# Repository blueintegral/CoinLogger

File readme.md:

CoinLogger
==========

CoinLogger is a US Quarter sized data logging platform. The current incantation has an accelerometer on it and 8 MB of Flash storage. It is based on the ATTiny85 microcontroller and also includes a USB port for retrieving the captured data. It was designed with a small size and extremely low power consumption in mind.

NanoLogger is a smaller version of CoinLogger, coming in at about the size of a dime, just over 15mm across. It doesn't have a USB port because there's no room. Instead, you need something like this: https://www.sparkfun.com/products/9235. The battery is smaller, so the battery life is substantially less, and programming and reading data off the device is done via small pads below the battery. This is best done with pogo pins, or you can solder to them. NanoLogger was designed to sacrifice some usability in exchange for an extremely small size.

Uses:
-----
* Amateur rocketry
* Tracking and alerting upon concussions in impact sports
* Characterizing your favorite rollercoaster
* Whatever else you can think of

Future Plans:
-------------
* Add versions with more/different sensors
* Make it even smaller
* Make a version that uses energy harvesting and remove the need for a battery
* Add a low power transciever?
* Move to FRAM instead of Flash, since FRAM can be lower power

Current State:
--------------
Version 1.1 of the boards has been fabbed and is being tested. Firmware is still being written. A program to pull data off the device over USB is also under development. 

Fabbed v1.1 CoinLogger:

Fabbed v1 NanoLogger:

Old v1:

Breadboarded circuit:

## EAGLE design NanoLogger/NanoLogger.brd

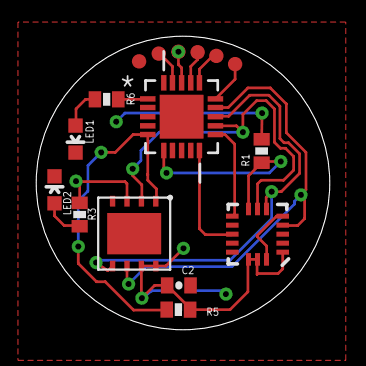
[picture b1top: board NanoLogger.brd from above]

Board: 4 copper layers, 16.3 x 16.3 mm, 17 parts (1 on the bottom side), 16 nets.

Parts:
/RESET: TPTP08R; TP08R
C2: 0.1uF; 0402-CAP
GND: TPTP08R; TP08R
LED1, LED2: LED-0603
MISO: TPTP08R; TP08R
MOSI: TPTP08R; TP08R
R1, R5: 10k; 0402-RES
R3, R6: 470; 0402-RES
SCK: TPTP08R; TP08R
U1: ATTINY2313-20MU; QFN50P400X400X80-21N
U4: LIS331; LGA16-3MM
U$1: ML621-TZ1
U$2: MX25U8035EZUI-10G
VCC: TPTP08R; TP08R

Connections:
ADI: U1.13, U4.6, U$2.5
ADO: U1.12, U4.7, U$2.2
ASCK: U1.14, U4.4, U$2.6
GND: C2.2, GND.TP, LED1.C, LED2.C, R1.2, U1.8, U1.21, U4.5, U4.10, U4.12, U4.13, U4.16, U$1.P$2, U$2.4, U$2.9
IMUCS: R1.1, U1.6, U4.8
INT1: U1.10, U4.11
INT2: U1.11, U4.9
MEMCS: R5.1, U1.5, U$2.1
unnamed: R6.2, U1.1
unnamed: /RESET.TP, U1.19
unnamed: LED2.A, R3.1
unnamed: SCK.TP, U1.17
unnamed: LED1.A, R6.1
unnamed: MISO.TP, U1.16
unnamed: MOSI.TP, U1.15
VCC: C2.1, R3.2, R5.2, U1.18, U4.1, U4.14, U4.15, U$1.P$1, U$2.3, U$2.7, U$2.8, VCC.TP

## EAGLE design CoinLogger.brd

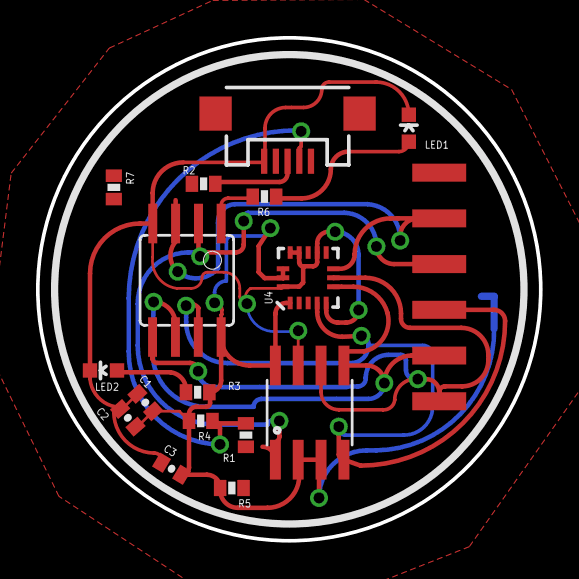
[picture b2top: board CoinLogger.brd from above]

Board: 2 copper layers, 27.9 x 27.9 mm, 18 parts (1 on the bottom side), 12 nets.

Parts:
BAT1: BATTCON_20MM
C1, C3: 10uF; 0402-CAP
C2: 0.1uF; 0402-CAP
IC1: TINY11S; SOIC8
JP2: 1X06-SMD_EDGE
LED1, LED2: LED-0603
R1, R2: 68; 0402-RES
R3, R6: 470; 0402-RES
R4: 1.5k; 0402-RES
R5: 10k; 0402-RES
R7: 4.7k; 0402-RES
U4: LIS331; LGA16-3MM
U$1: W25Q80BV; SOIC8
X1: USB-MICROB

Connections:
GND: BAT1.2, C1.2, C2.2, C3.2, IC1.4, JP2.5, LED1.C, LED2.C, U4.5, U4.10, U4.12, U4.13, U4.16, U$1.7, X1.GND
unnamed: R2.2, X1.D+
unnamed: LED2.A, R3.1
unnamed: IC1.2, JP2.4, R2.1, R5.1, U4.8, U$1.1
unnamed: IC1.7, JP2.3, U4.4, U$1.4
unnamed: IC1.5, JP2.1, U4.7, U4.11, U$1.6
unnamed: IC1.6, JP2.2, U4.6, U$1.5
unnamed: R1.2, R4.1, X1.D-
unnamed: IC1.1, R7.1
unnamed: LED1.A, R6.1
unnamed: IC1.3, R1.1, R6.2
VCC: BAT1.1, C1.1, C2.1, C3.1, IC1.8, JP2.6, R3.2, R4.2, R5.2, R7.2, U4.1, U4.14, U4.15, U$1.2, U$1.3, U$1.8

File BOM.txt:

Partlist

Exported from CoinLogger.sch at 12/19/2013 10:44:44 PM

EAGLE Version 6.2.0 Copyright (c) 1988-2012 CadSoft

Assembly variant: 

Part     Value           Device                  Package        Library  Sheet

BAT2                     BATTERY20SMD            BATTCON_20MM   SparkFun 1
C1       10uF            CAP0402-CAP             0402-CAP       SparkFun 1
C2       0.1uF           CAP0402-CAP             0402-CAP       SparkFun 1
C3       10uF            CAP0402-CAP             0402-CAP       SparkFun 1
IC1      TINY11S         TINY11S                 SOIC8          atmel    1
JP1      USB_MICROB_PLUG USB_MICROB_PLUG         MICRO-B-RA-SMT SparkFun 1
JP2                      M061X06-SMD_EDGE_FEMALE 1X06-SMD_EDGE  SparkFun 1
LED1                     LED0603                 LED-0603       SparkFun 1
LED2                     LED0603                 LED-0603       SparkFun 1
R1       68              RESISTOR0402-RES        0402-RES       SparkFun 1
R2       68              RESISTOR0402-RES        0402-RES       SparkFun 1
R3       470             RESISTOR0402-RES        0402-RES       SparkFun 1
R4       1.5k            RESISTOR0402-RES        0402-RES       SparkFun 1
R5       10k             RESISTOR0402-RES        0402-RES       SparkFun 1
R6       470             RESISTOR0402-RES        0402-RES       SparkFun 1
U$1      W25Q80BV        W25Q80BV                SOIC8          W25Q80BV 1
U4       LIS331          LIS331                  LGA16-3MM      SparkFun 1

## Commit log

2013-12-20 Added note for future rev
2014-01-05 Added some test code, started v1.1 of board
2014-01-05 Cleaned up repo organization
2014-01-05 Added pictures to readme
2014-01-05 captions
2014-01-06 Board is now v1.1
2014-01-07 Lots of fixes, added NanoLogger
2014-01-07 Updated and rerouted V1.1, early nanologger layout
2014-01-08 NanoLogger is routed and ready for order. 16mm!
2014-02-19 Updated readme, test code kinda works now
2014-02-19 Boring readme stuff
2014-02-19 blah
2014-02-19 are you KIDDING ME
2014-02-20 accel test
2014-03-01 Programming issue workaround
2014-05-07 spliced some stuff for an arduino verison
2015-06-29 well, it's routed...
2015-06-29 Route looks better now
2015-06-29 Quick ERC fix, removed temp files

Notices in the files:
parts and their libraries:
SparkFun: Licensing: CC v3.0 Share-Alike You are welcome to use this library for commercial purposes.
